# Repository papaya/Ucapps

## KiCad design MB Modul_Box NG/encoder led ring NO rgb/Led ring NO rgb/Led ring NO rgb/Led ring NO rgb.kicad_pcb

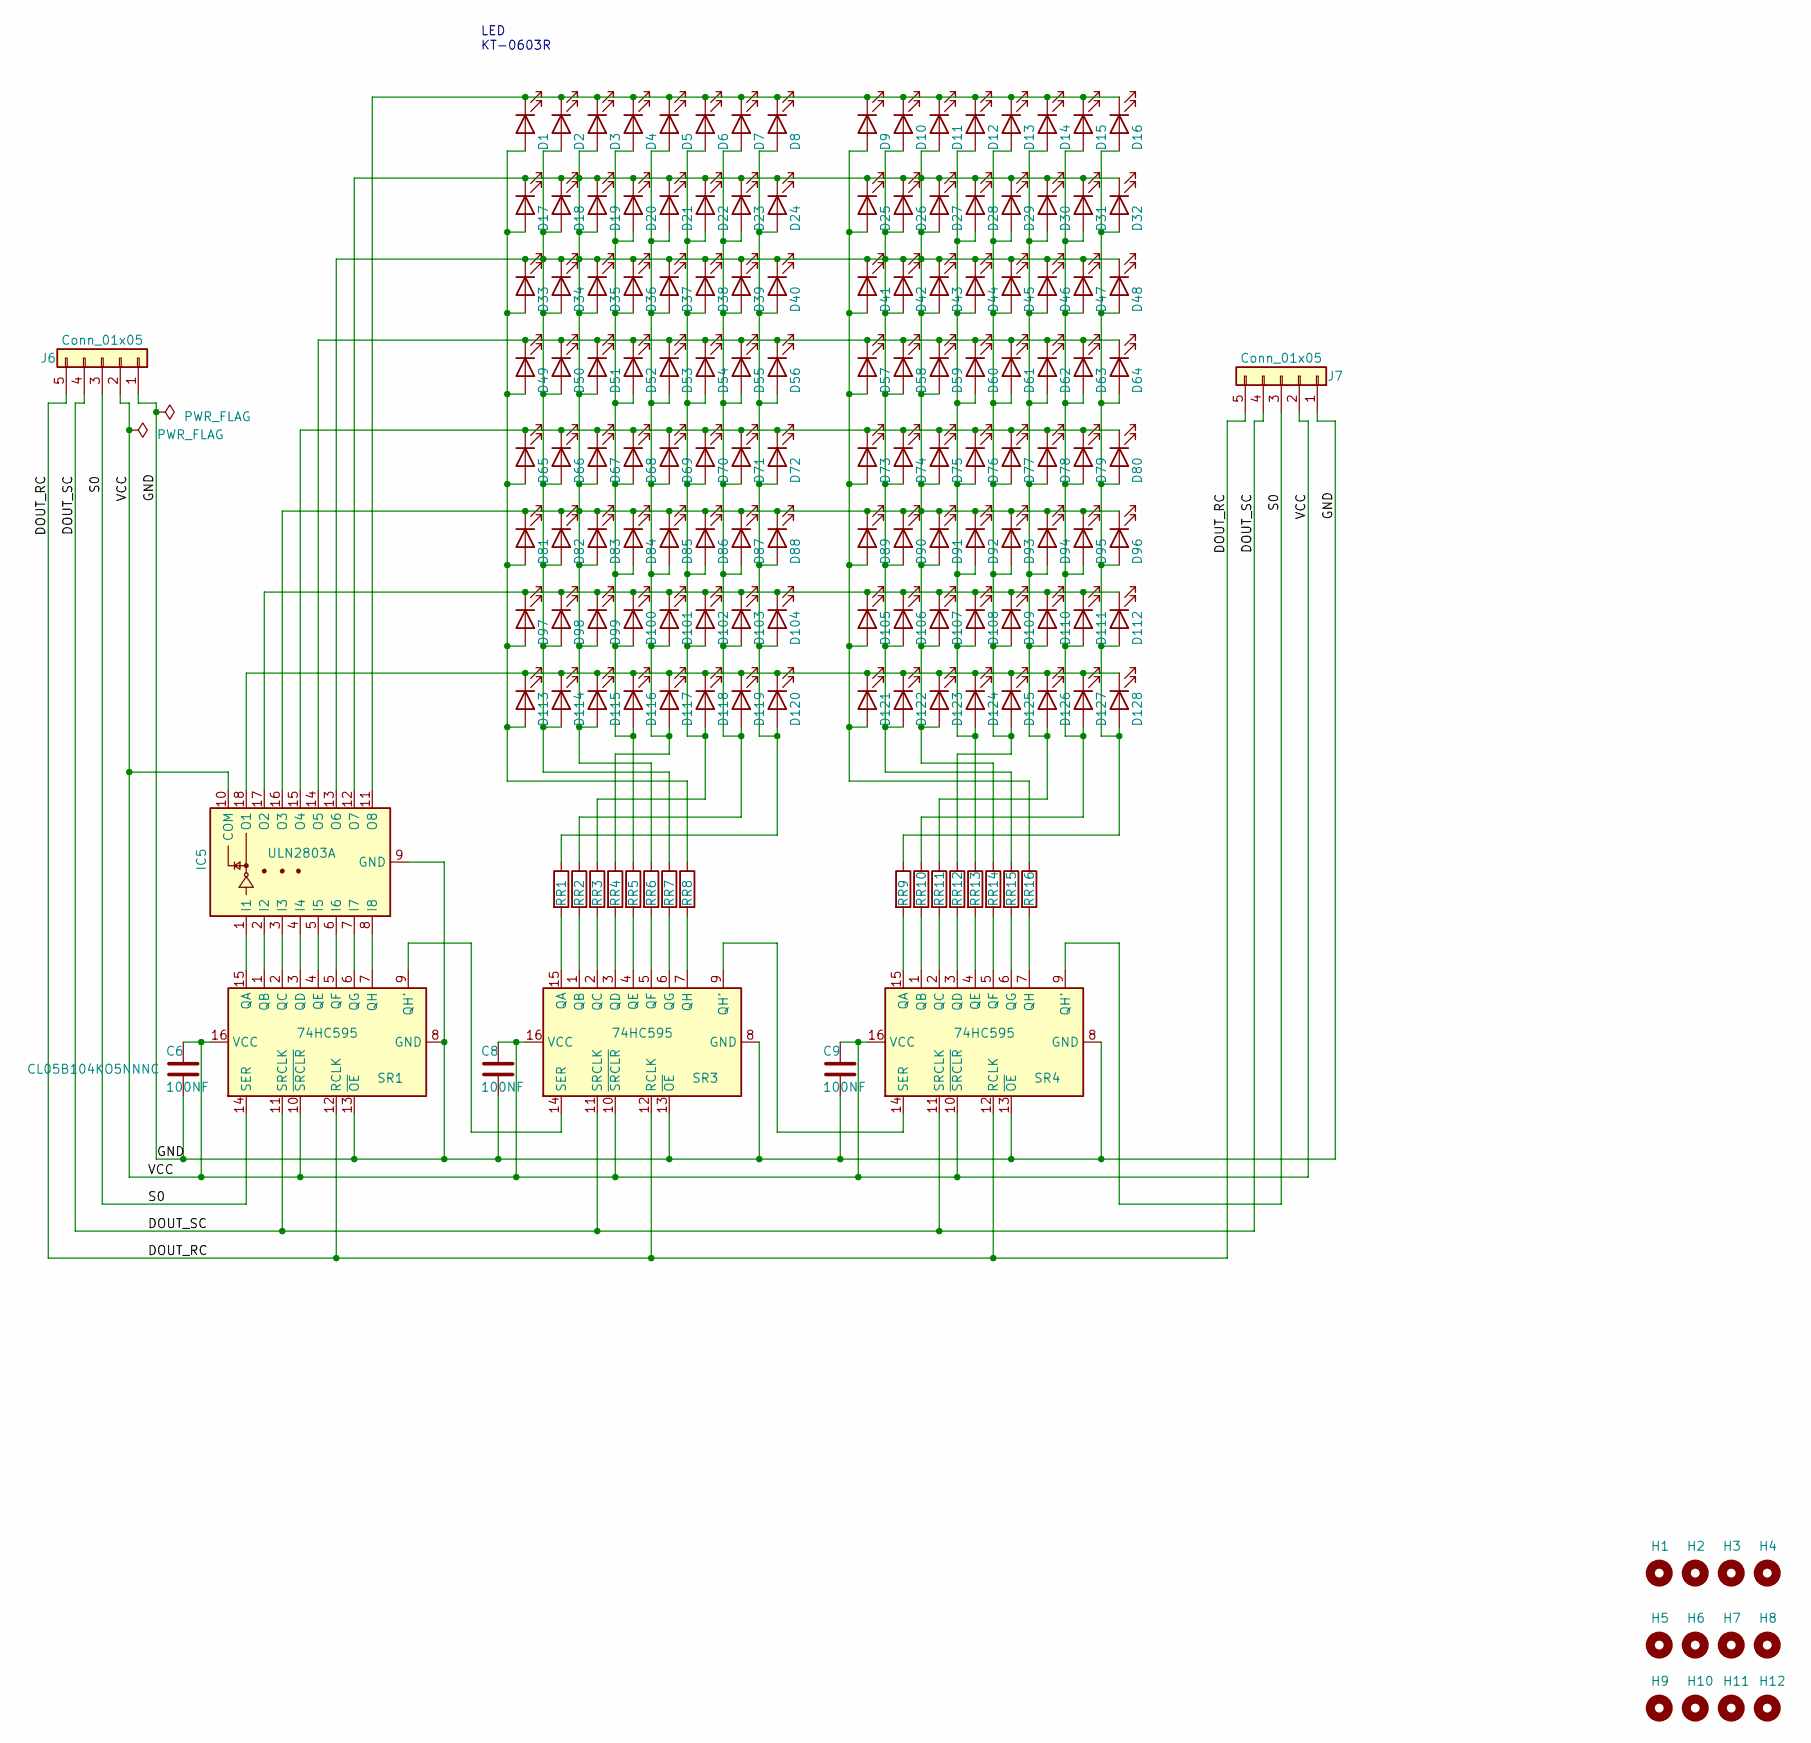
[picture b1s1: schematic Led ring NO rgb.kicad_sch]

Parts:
C6, C8, C9: 100NF; CAPC1005X55N
D1, D2, D3, D4, D5, D6, D7, D8, D9, D10, D11, D12, D13, D14, D15, D16, D17, D18, D19, D20, D21, D22, D23, D24, D25, D26, D27, D28, D29, D30, D31, D32, D33, D34, D35, D36, D37, D38, D39, D40, D41, D42, D43, D44, D45, D46, D47, D48, D49, D50, D51, D52, D53, D54, D55, D56, D57, D58, D59, D60, D61, D62, D63, D64, D65, D66, D67, D68, D69, D70, D71, D72, D73, D74, D75, D76, D77, D78, D79, D80, D81, D82, D83, D84, D85, D86, D87, D88, D89, D90, D91, D92, D93, D94, D95, D96, D97, D98, D99, D100, D101, D102, D103, D104, D105, D106, D107, D108, D109, D110, D111, D112, D113, D114, D115, D116, D117, D118, D119, D120, D121, D122, D123, D124, D125, D126, D127, D128: LED; LEDC1608X70N
H1, H2, H3, H4: MountingHole; MountingHole_3.2mm_M3
H5, H6, H7, H8, H9, H10, H11, H12: MountingHole; MountingHole_6.5mm
IC5: ULN2803A; uln2803SMD_SOIC127P1030X265-18N
J6, J7: Conn_01x05; PinSocket_1x05_P2.54mm_Vertical
R1, R2, R3, R4, R5, R6, R7, R8, R9, R10, R11, R12, R13, R14, R15, R16: R; R_0805_2012Metric
SR1, SR3, SR4: 74HC595; 74hc595n_SOIC127P600X175-16N

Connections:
/DOUT_RC: J6.5, J7.5, SR1.12 (RCLK), SR3.12 (RCLK), SR4.12 (RCLK)
/DOUT_SC: J6.4, J7.4, SR1.11 (SRCLK), SR3.11 (SRCLK), SR4.11 (SRCLK)
/GND: C6.1, C8.1, C9.1, IC5.9 (GND), J6.1, J7.1, SR1.8 (GND), SR1.13 (~OE), SR3.8 (GND), SR3.13 (~OE), SR4.8 (GND), SR4.13 (~OE)
/S0: J6.3, J7.3, SR1.14 (SER), SR4.9 (QH')
/VCC: C6.2, C8.2, C9.2, IC5.10 (COM), J6.2, J7.2, SR1.10 (~SRCLR), SR1.16 (VCC), SR3.10 (~SRCLR), SR3.16 (VCC), SR4.10 (~SRCLR), SR4.16 (VCC)
unnamed: D1.2 (A), D17.2 (A), D33.2 (A), D49.2 (A), D65.2 (A), D81.2 (A), D97.2 (A), D113.2 (A), R8.1
unnamed: D1.1 (K), D2.1 (K), D3.1 (K), D4.1 (K), D5.1 (K), D6.1 (K), D7.1 (K), D8.1 (K), D9.1 (K), D10.1 (K), D11.1 (K), D12.1 (K), D13.1 (K), D14.1 (K), D15.1 (K), D16.1 (K), IC5.11 (O8)
unnamed: D2.2 (A), D3.2 (A), D10.2 (A), D11.2 (A), D17.1 (K), D18.1 (K), D18.2 (A), D19.1 (K), D19.2 (A), D20.1 (K), D21.1 (K), D22.1 (K), D23.1 (K), D24.1 (K), D25.1 (K), D26.1 (K), D26.2 (A), D27.1 (K), D27.2 (A), D28.1 (K), D29.1 (K), D30.1 (K), D31.1 (K), D32.1 (K), D33.1 (K), D34.1 (K), D34.2 (A), D35.1 (K), D35.2 (A), D36.1 (K), D37.1 (K), D38.1 (K), D39.1 (K), D40.1 (K), D41.1 (K), D42.1 (K), D42.2 (A), D43.1 (K), D43.2 (A), D44.1 (K), D45.1 (K), D46.1 (K), D47.1 (K), D48.1 (K), D50.2 (A), D51.2 (A), D58.2 (A), D59.2 (A), D66.2 (A), D67.2 (A), D74.2 (A), D75.2 (A), D81.1 (K), D82.1 (K), D82.2 (A), D83.1 (K), D83.2 (A), D84.1 (K), D85.1 (K), D86.1 (K), D87.1 (K), D88.1 (K), D89.1 (K), D90.1 (K), D90.2 (A), D91.1 (K), D91.2 (A), D92.1 (K), D93.1 (K), D94.1 (K), D95.1 (K), D96.1 (K), D98.2 (A), D99.2 (A), D106.2 (A), D107.2 (A), D114.2 (A), D115.2 (A), D122.2 (A), D123.2 (A), IC5.12 (O7), IC5.13 (O6), IC5.16 (O3), R6.1, R7.1, R14.1, R15.1
unnamed: D49.1 (K), D50.1 (K), D51.1 (K), D52.1 (K), D53.1 (K), D54.1 (K), D55.1 (K), D56.1 (K), D57.1 (K), D58.1 (K), D59.1 (K), D60.1 (K), D61.1 (K), D62.1 (K), D63.1 (K), D64.1 (K), IC5.14 (O5)
unnamed: D65.1 (K), D66.1 (K), D67.1 (K), D68.1 (K), D69.1 (K), D70.1 (K), D71.1 (K), D72.1 (K), D73.1 (K), D74.1 (K), D75.1 (K), D76.1 (K), D77.1 (K), D78.1 (K), D79.1 (K), D80.1 (K), IC5.15 (O4)
unnamed: D4.2 (A), D20.2 (A), D36.2 (A), D52.2 (A), D68.2 (A), D84.2 (A), D100.2 (A), D116.2 (A), R5.1
unnamed: D97.1 (K), D98.1 (K), D99.1 (K), D100.1 (K), D101.1 (K), D102.1 (K), D103.1 (K), D104.1 (K), D105.1 (K), D106.1 (K), D107.1 (K), D108.1 (K), D109.1 (K), D110.1 (K), D111.1 (K), D112.1 (K), IC5.17 (O2)
unnamed: D5.2 (A), D21.2 (A), D37.2 (A), D53.2 (A), D69.2 (A), D85.2 (A), D101.2 (A), D117.2 (A), R4.1
unnamed: D6.2 (A), D22.2 (A), D38.2 (A), D54.2 (A), D70.2 (A), D86.2 (A), D102.2 (A), D118.2 (A), R3.1
unnamed: D7.2 (A), D23.2 (A), D39.2 (A), D55.2 (A), D71.2 (A), D87.2 (A), D103.2 (A), D119.2 (A), R2.1
unnamed: D8.2 (A), D24.2 (A), D40.2 (A), D56.2 (A), D72.2 (A), D88.2 (A), D104.2 (A), D120.2 (A), R1.1
unnamed: D9.2 (A), D25.2 (A), D41.2 (A), D57.2 (A), D73.2 (A), D89.2 (A), D105.2 (A), D121.2 (A), R16.1
unnamed: D12.2 (A), D28.2 (A), D44.2 (A), D60.2 (A), D76.2 (A), D92.2 (A), D108.2 (A), D124.2 (A), R13.1
unnamed: D13.2 (A), D29.2 (A), D45.2 (A), D61.2 (A), D77.2 (A), D93.2 (A), D109.2 (A), D125.2 (A), R12.1
unnamed: D14.2 (A), D30.2 (A), D46.2 (A), D62.2 (A), D78.2 (A), D94.2 (A), D110.2 (A), D126.2 (A), R11.1
unnamed: D15.2 (A), D31.2 (A), D47.2 (A), D63.2 (A), D79.2 (A), D95.2 (A), D111.2 (A), D127.2 (A), R10.1
unnamed: D16.2 (A), D32.2 (A), D48.2 (A), D64.2 (A), D80.2 (A), D96.2 (A), D112.2 (A), D128.2 (A), R9.1
unnamed: D113.1 (K), D114.1 (K), D115.1 (K), D116.1 (K), D117.1 (K), D118.1 (K), D119.1 (K), D120.1 (K), D121.1 (K), D122.1 (K), D123.1 (K), D124.1 (K), D125.1 (K), D126.1 (K), D127.1 (K), D128.1 (K), IC5.18 (O1)
unnamed: IC5.1 (I1), SR1.15 (QA)
unnamed: IC5.2 (I2), SR1.1 (QB)
unnamed: IC5.3 (I3), SR1.2 (QC)
unnamed: IC5.4 (I4), SR1.3 (QD)
unnamed: IC5.5 (I5), SR1.4 (QE)
unnamed: IC5.6 (I6), SR1.5 (QF)
unnamed: IC5.7 (I7), SR1.6 (QG)
unnamed: IC5.8 (I8), SR1.7 (QH)
unnamed: SR1.9 (QH'), SR3.14 (SER)
unnamed: R1.2, SR3.15 (QA)
unnamed: R2.2, SR3.1 (QB)
unnamed: R3.2, SR3.2 (QC)
unnamed: R4.2, SR3.3 (QD)
unnamed: R5.2, SR3.4 (QE)
unnamed: R6.2, SR3.5 (QF)
unnamed: R7.2, SR3.6 (QG)
unnamed: SR3.9 (QH'), SR4.14 (SER)
unnamed: R8.2, SR3.7 (QH)
unnamed: R9.2, SR4.15 (QA)
unnamed: R10.2, SR4.1 (QB)
unnamed: R11.2, SR4.2 (QC)
unnamed: R12.2, SR4.3 (QD)
unnamed: R13.2, SR4.4 (QE)
unnamed: R14.2, SR4.5 (QF)
unnamed: R15.2, SR4.6 (QG)
unnamed: R16.2, SR4.7 (QH)

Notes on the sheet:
LED KT-0603R

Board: 2 copper layers, 165 parts (25 on the bottom side), 49 nets, no tracks yet.

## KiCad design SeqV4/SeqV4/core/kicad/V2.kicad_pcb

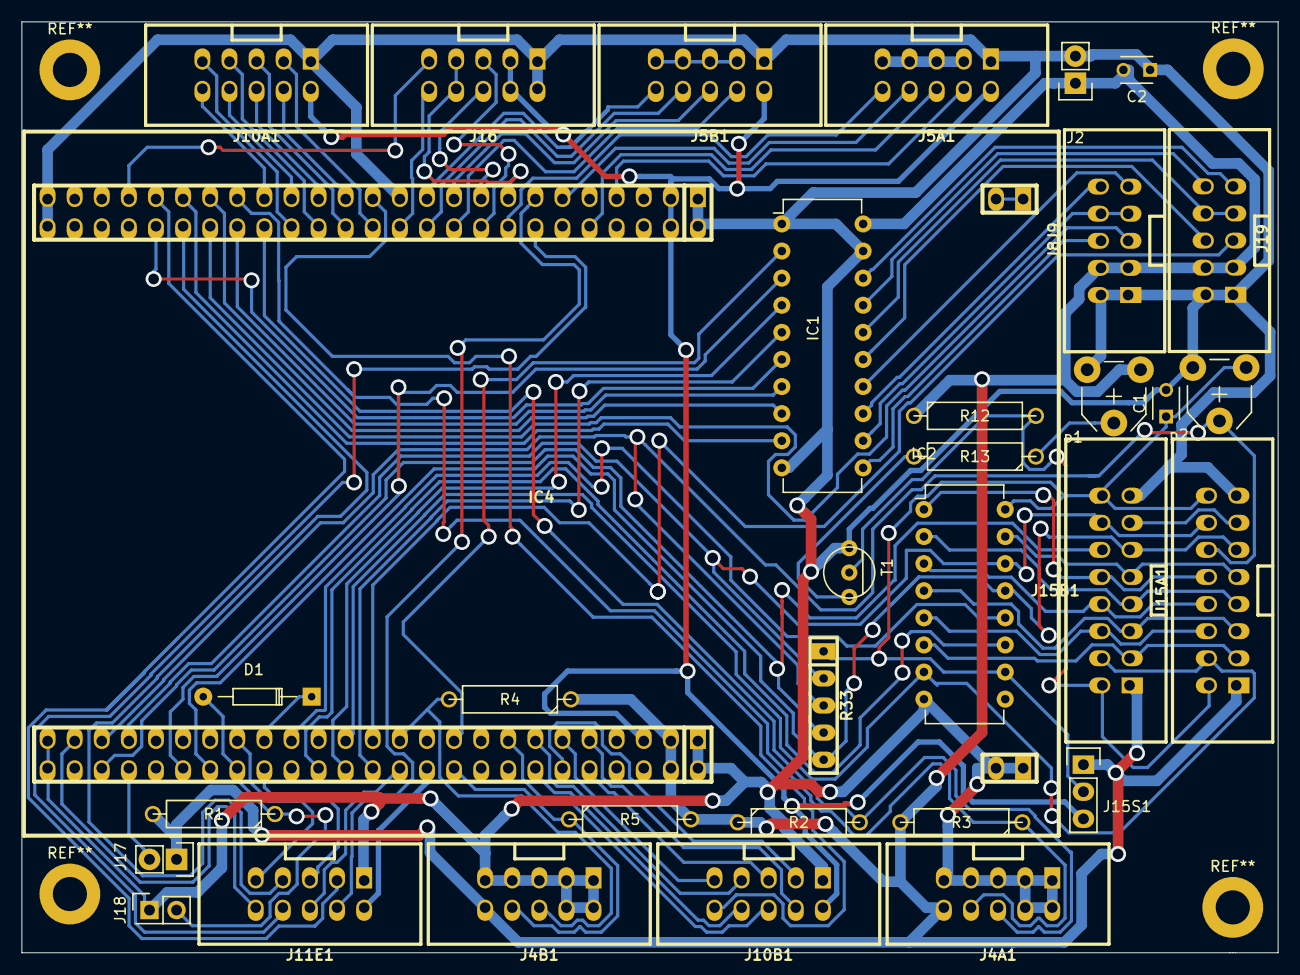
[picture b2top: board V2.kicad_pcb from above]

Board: 2 copper layers, 117.8 x 87.2 mm, 33 parts (0 on the bottom side), 86 nets.

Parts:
C1, C2: C; C_Disc_D3_P2.5
D1: D; Diode_DO-35_SOD27_Horizontal_RM10
IC1: 74HCT541_PWR; DIP-20_W7.62mm
IC2: 74HC595; DIP-16_W7.62mm
IC4: STM32F4_Discovery_Header; stm32f4_discovery_header
J2: CONN_2; Pin_Header_Straight_1x02
J4A1, J4B1, J5A1, J5B1, J8J9, J10A1, J10B1, J11E1, J16, J19: CONN_02X05; vasch_strip_5x2
J15A1, J15B1: CONN_02X08; vasch_strip_8x2
J15S1: CONN_01X03; Pin_Header_Straight_1x03
J17: CONN_01X02; Pin_Header_Straight_1x02
J18: CONN_2; Pin_Header_Straight_2x01
R1, R2, R3, R4, R5, R12, R13: R; R4-5
R33: R-SIL_4; r-sil_5
T1: BC817-40; bc337
p1, p2: POT; Potentiometer_VishaySpectrol-Econtrim-Type36T

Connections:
+3V3: IC4.3, IC4.4, IC4.80, IC4.95, J5A1.2, J5B1.2, J10A1.2, J10B1.2, J11E1.2, J15S1.3, J16.3, J16.4
+5V: C2.2, IC1.20, IC4.97, IC4.98, J2.1, J4A1.10, J4B1.10, J8J9.3, J8J9.4, J15A1.1, J15B1.1, J15S1.1, J17.1, J19.3, J19.4, R1.2, R2.1, R3.2, R4.1, R5.2, R12.1, p1.1
/PA1: IC4.11, J5A1.8
/PA2: IC4.14, J11E1.8
/PA3: IC4.13, J11E1.4
/PA4: IC4.16, J5A1.10
/PA5: IC4.15, J16.7, J16.8
/PA6: IC4.18, J16.5
/PA7: IC4.17, J16.6
/PA8: IC2.14, IC4.57, J15A1.14, J15B1.14, R33.2
/PA9: IC4.58, J17.2
/PA15: IC1.3, IC4.62
/PB0: IC4.22, J5B1.8
/PB1: IC4.21, J5B1.10
/PB2: IC4.24, J16.10
/PB3: IC1.4, IC4.74
/PB4: IC4.75, J19.5
/PB5: IC1.5, IC4.76
/PB6: IC4.77, J4B1.6, R4.2
/PB7: IC4.78, J11E1.6
/PB8: IC1.2, IC4.81
/PB9: IC4.82, J4B1.8, R5.1
/PB10: IC4.34, J4A1.6, R2.2
/PB11: IC4.35, J4A1.8, R3.1
/PB12: IC1.7, IC4.36
/PB13: IC1.8, IC4.37
/PB14: IC4.38, J8J9.5
/PB15: IC1.9, IC4.39
/PC1: IC4.7, J5A1.4
/PC2: IC4.10, J5A1.6
/PC4: IC4.20, J5B1.4
/PC5: IC4.19, J5B1.6
/PC6: IC4.53, J11E1.10
/PC8: IC4.55, J15A1.12, R33.3, p2.2
/PC9: IC4.56, J15B1.12, R33.4
/PC11: IC2.13, IC4.64, J15A1.11, J15B1.11, R33.5
/PC12: IC4.65, J11E1.9
/PC13: IC4.90, J10B1.3
/PC14: IC4.91, J10B1.4
/PC15: IC4.92, J10B1.5
/PD0: D1.2, IC4.66, J18.2, R1.1
/PD1: D1.1, IC4.67
/PD2: IC4.68, J11E1.5
/PD3: IC2.12, IC4.69
/PD6: IC2.11, IC4.72
/PD7: IC2.7, IC4.73, J15A1.4, J15B1.4
/PD8: IC4.40, J11E1.7
/PD9: IC4.41, J11E1.3
/PD10: IC1.6, IC4.42
/PD11: IC4.43, J16.9
/PE2: IC4.85, J10B1.6
/PE4: IC4.87, J10B1.7
/PE5: IC4.88, J10B1.8
/PE6: IC4.89, J10B1.9
/PE7: IC4.25, J10B1.10
/PE8: IC4.26, J10A1.3
/PE9: IC4.27, J10A1.4
/PE10: IC4.28, J10A1.5
/PE11: IC4.29, J10A1.6
/PE12: IC4.30, J10A1.7
/PE13: IC4.31, J10A1.8
/PE14: IC4.32, J10A1.9
/PE15: IC4.33, J10A1.10
GND: C1.2, C2.1, IC1.1, IC1.10, IC1.19, IC2.8, IC4.1, IC4.2, IC4.5, IC4.23, IC4.49, IC4.50, IC4.51, IC4.52, IC4.99, IC4.100, J2.2, J4A1.1, J4A1.2, J4A1.3, J4A1.4, J4A1.5, J4A1.7, J4A1.9, J4B1.1, J4B1.2, J4B1.3, J4B1.4, J4B1.5, J4B1.7, J4B1.9, J5A1.1, J5B1.1, J8J9.1, J8J9.2, J10A1.1, J10B1.1, J11E1.1, J15A1.15, J15B1.15, J16.1, J16.2, J18.1, J19.1, J19.2, T1.2, p1.3, p2.3
unnamed: C1.1, IC2.10, IC2.16, J15A1.16, J15B1.16, J15S1.2, R33.1, p2.1
unnamed: IC1.11, J8J9.6
unnamed: IC1.12, J8J9.7, J8J9.8
unnamed: IC1.13, J8J9.10
unnamed: IC1.14, J8J9.9
unnamed: IC1.15, J19.6
unnamed: IC1.16, J19.7, J19.8
unnamed: IC1.17, J19.10
unnamed: IC1.18, J19.9
unnamed: IC2.1, J15A1.10, J15B1.10
unnamed: IC2.2, J15A1.7, J15B1.7
unnamed: IC2.3, J15A1.8, J15B1.8
unnamed: IC2.4, J15A1.5, J15B1.5
unnamed: IC2.5, J15A1.6, J15B1.6
unnamed: IC2.6, J15A1.3, J15B1.3
unnamed: IC2.15, J15A1.9, J15B1.9
unnamed: J5A1.3, J5A1.5, J5A1.7, J5A1.9
unnamed: J5B1.3, J5B1.5, J5B1.7, J5B1.9
unnamed: J15A1.2, J15B1.2, R12.2, T1.3
unnamed: J15A1.13, J15B1.13
unnamed: R13.1, p1.2
unnamed: R13.2, T1.1

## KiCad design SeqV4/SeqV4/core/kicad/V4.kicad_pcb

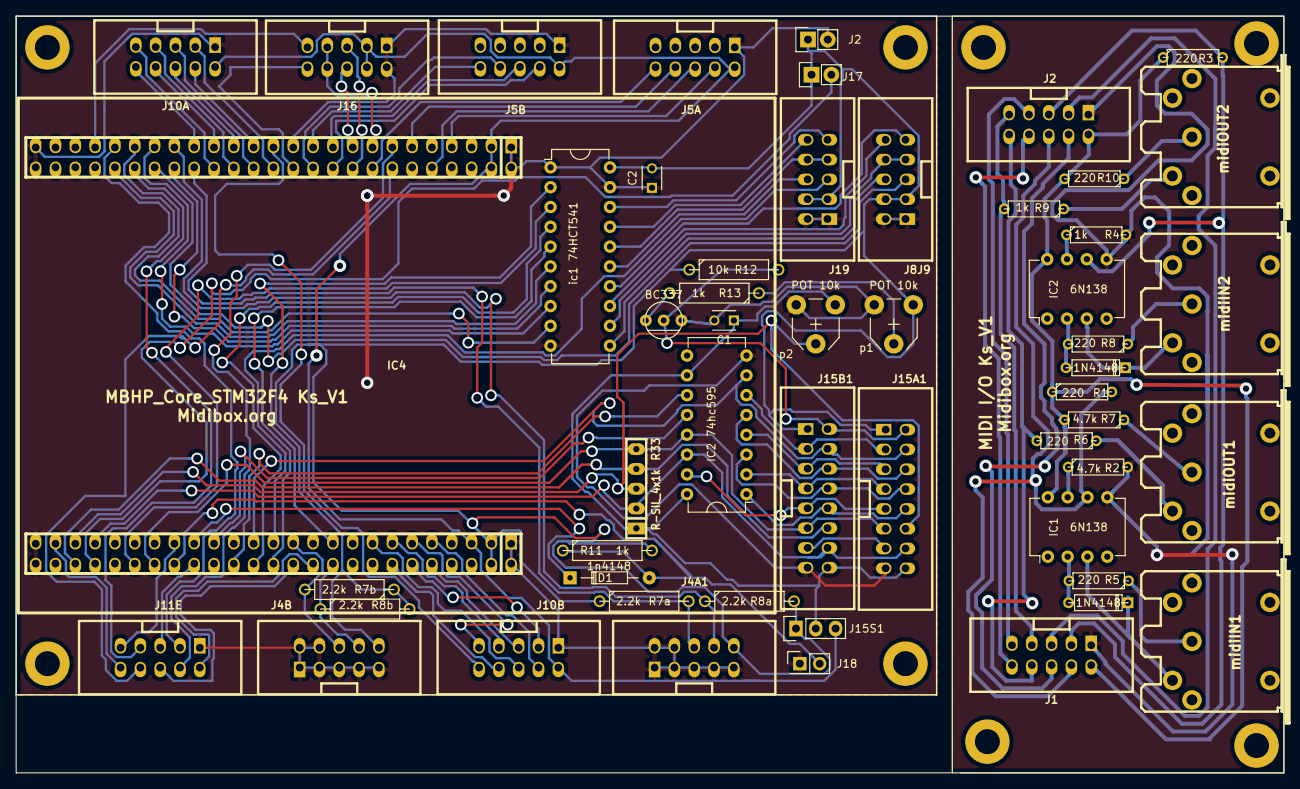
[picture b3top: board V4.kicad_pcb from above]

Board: 2 copper layers, 162.5 x 97.0 mm, 50 parts (0 on the bottom side), 104 nets.

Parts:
C1, C2: C; C_Disc_D3_P2.5
D1: 1n4148; Diode_DO-35_SOD27_Horizontal_RM10
IC1, IC2: 6N138; DIP-8_W7.62mm
IC2 74hc595: 74HC595; DIP-16_W7.62mm
IC4: STM32F4_Discovery_Header; stm32f4_discovery_header
J1, J2#2, J4A1, J4B, J5A, J5B, J8J9, J10A, J10B, J11E, J16, J19: CONN_02X05; vasch_strip_5x2
J2: CONN_2; Pin_Header_Straight_1x02
J15A1, J15B1: CONN_02X08; vasch_strip_8x2
J15S1: CONN_01X03; Pin_Header_Straight_1x03
J17: CONN_01X02; Pin_Header_Straight_1x02
J18: CONN_2; Pin_Header_Straight_2x01
R1, R3, R5, R6, R8, R10: 220; R3
R2, R7: 4.7k; R3
R4, R9: 1k; R3
R7a, R7b, R8a, R8b: 2.2k; R4-5
R11, R13: 1k; R4-5
R12: 10k; R4-5
R33: R-SIL_4x1k; r-sil_5
ic1 74HCT541: 74HCT541; DIP-20_W7.62mm
midiIN1, midiIN2: din-5
midiOUT1, midiOUT2: din-5
p1, p2: POT 10k; Potentiometer_VishaySpectrol-Econtrim-Type36T

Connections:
+3V3: IC4.3, IC4.4, IC4.80, IC4.95, J5A.2, J5B.2, J10A.2, J10B.2, J11E.2, J15S1.3, J16.3, J16.4
+5V: C2.2, IC1.8, IC2.8, IC4.97, IC4.98, J1.2, J2.1, J2#2.2, J4A1.10, J4B.10, J8J9.3, J8J9.4, J15A1.1, J15B1.1, J15S1.1, J17.1, J19.3, J19.4, R1.1, R3.1, R7.2, R7a.1, R7b.1, R8a.2, R8b.2, R10.2, R11.2, R12.1, ic1 74HCT541.20, p1.1
/PA1: IC4.11, J5A.8
/PA2: IC4.14, J11E.8
/PA3: IC4.13, J11E.4
/PA4: IC4.16, J5A.10
/PA5: IC4.15, J16.7, J16.8
/PA6: IC4.18, J16.5
/PA7: IC4.17, J16.6
/PA8: IC2 74hc595.14, IC4.57, J15A1.14, J15B1.14, R33.2
/PA9: IC4.58, J17.2
/PA15: IC4.62, ic1 74HCT541.3
/PB0: IC4.22, J5B.8
/PB1: IC4.21, J5B.10
/PB2: IC4.24, J16.10
/PB3: IC4.74, ic1 74HCT541.4
/PB4: IC4.75, J19.5
/PB5: IC4.76, ic1 74HCT541.5
/PB6: IC4.77, J4B.6, R7b.2
/PB7: IC4.78, J11E.6
/PB8: IC4.81, ic1 74HCT541.2
/PB9: IC4.82, J4B.8, R8b.1
/PB10: IC4.34, J4A1.6, R7a.2
/PB11: IC4.35, J4A1.8, R8a.1
/PB12: IC4.36, ic1 74HCT541.7
/PB13: IC4.37, ic1 74HCT541.8
/PB14: IC4.38, J8J9.5
/PB15: IC4.39, ic1 74HCT541.9
/PC1: IC4.7, J5A.4
/PC2: IC4.10, J5A.6
/PC4: IC4.20, J5B.4
/PC5: IC4.19, J5B.6
/PC6: IC4.53, J11E.10
/PC8: IC4.55, J15A1.12, R33.3, p2.2
/PC9: IC4.56, J15B1.12, R33.4
/PC11: IC2 74hc595.13, IC4.64, J15A1.11, J15B1.11, R33.5
/PC12: IC4.65, J11E.9
/PC13: IC4.90, J10B.3
/PC14: IC4.91, J10B.4
/PC15: IC4.92, J10B.5
/PD0: D1.2, IC4.66, J18.2, R11.1
/PD1: D1.1, IC4.67
/PD2: IC4.68, J11E.5
/PD3: IC2 74hc595.12, IC4.69
/PD6: IC2 74hc595.11, IC4.72
/PD7: IC2 74hc595.7, IC4.73, J15A1.4, J15B1.4
/PD8: IC4.40, J11E.7
/PD9: IC4.41, J11E.3
/PD10: IC4.42, ic1 74HCT541.6
/PD11: IC4.43, J16.9
/PE2: IC4.85, J10B.6
/PE4: IC4.87, J10B.7
/PE5: IC4.88, J10B.8
/PE6: IC4.89, J10B.9
/PE7: IC4.25, J10B.10
/PE8: IC4.26, J10A.3
/PE9: IC4.27, J10A.4
/PE10: IC4.28, J10A.5
/PE11: IC4.29, J10A.6
/PE12: IC4.30, J10A.7
/PE13: IC4.31, J10A.8
/PE14: IC4.32, J10A.9
/PE15: IC4.33, J10A.10
GND: C1.2, C2.1, IC1.5, IC2.5, IC2 74hc595.8, IC4.1, IC4.2, IC4.5, IC4.23, IC4.49, IC4.50, IC4.51, IC4.52, IC4.99, IC4.100, J1.1, J2.2, J2#2.1, J4A1.1, J4A1.2, J4A1.3, J4A1.4, J4A1.5, J4A1.7, J4A1.9, J4B.1, J4B.2, J4B.3, J4B.4, J4B.5, J4B.7, J4B.9, J5A.1, J5B.1, J8J9.1, J8J9.2, J10A.1, J10B.1, J11E.1, J15A1.15, J15B1.15, J16.1, J16.2, J18.1, J19.1, J19.2, R2.2, R4.2, ic1 74HCT541.1, ic1 74HCT541.10, ic1 74HCT541.19, p1.3, p2.3
unnamed: C1.1, IC2 74hc595.10, IC2 74hc595.16, J15A1.16, J15B1.16, J15S1.2, R33.1, p2.1
unnamed: IC1.3, midiIN1.5
unnamed: IC1.2, R5.2
unnamed: IC2.3, midiIN2.5
unnamed: IC2.2, R8.2
unnamed: IC1.6, J1.4, J2#2.6, R1.2
unnamed: IC1.7, R2.1
unnamed: IC2 74hc595.1, J15A1.10, J15B1.10
unnamed: IC2 74hc595.2, J15A1.7, J15B1.7
unnamed: IC2 74hc595.3, J15A1.8, J15B1.8
unnamed: IC2 74hc595.4, J15A1.5, J15B1.5
unnamed: IC2 74hc595.5, J15A1.6, J15B1.6
unnamed: IC2.6, IC2 74hc595.6, J1.3, J2#2.5, J15A1.3, J15B1.3, R3.2
unnamed: IC2.7, R4.1
unnamed: IC2 74hc595.15, J15A1.9, J15B1.9
unnamed: J5A.3, J5A.5, J5A.7, J5A.9
unnamed: J5B.3, J5B.5, J5B.7, J5B.9
unnamed: J8J9.6, ic1 74HCT541.11
unnamed: J8J9.7, J8J9.8, ic1 74HCT541.12
unnamed: J8J9.9, ic1 74HCT541.14
unnamed: J8J9.10, ic1 74HCT541.13
unnamed: J15A1.2, J15B1.2, R12.2
unnamed: J15A1.13, J15B1.13
unnamed: J19.6, ic1 74HCT541.15
unnamed: J19.7, J19.8, ic1 74HCT541.16
unnamed: J19.9, ic1 74HCT541.18
unnamed: J19.10, ic1 74HCT541.17
unnamed: J1.5, J2#2.3
unnamed: J1.6, J2#2.4
unnamed: J1.7, J2#2.9, R9.2
unnamed: J1.8, J2#2.10, R6.2
unnamed: J1.9, J2#2.7
unnamed: J1.10, J2#2.8
unnamed: R5.1, midiIN1.2
unnamed: R6.1, midiOUT1.5
unnamed: R7.1, midiOUT1.2
unnamed: R8.1, midiIN2.2
unnamed: R9.1, midiOUT2.5
unnamed: R10.1, midiOUT2.2
unnamed: R13.1, p1.2
